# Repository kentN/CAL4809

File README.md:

# CAL4809
ATmega4809 TimeKeeping Module with MemoryLCD

----------

## Features ##

- ATmega4809 MCU (SRAM 6kB, FlashROM 48kB)
- Sharp Memory LCD (128x128pixcel or 96x96pixcel)
- 3 button
- Low Power Accelerometer ADXL362
- IrDA SIR Transceiver
- 32.768kHz External Crystal
- CR2032 Coin Cell battery (Diode OR option)
- External Connector(DF12-20p) 
- BUS UART(x2ch), SPI, I2C, GPIO/ADC(x8ch)

----------
## Applications ##

- DIY WristWatch
- Embedded Display&TimeKeeping module
- Motion Data Logger

----------

## Project Environment ##

- KiCad (5.0.1)
- Atmel Studio 7.0

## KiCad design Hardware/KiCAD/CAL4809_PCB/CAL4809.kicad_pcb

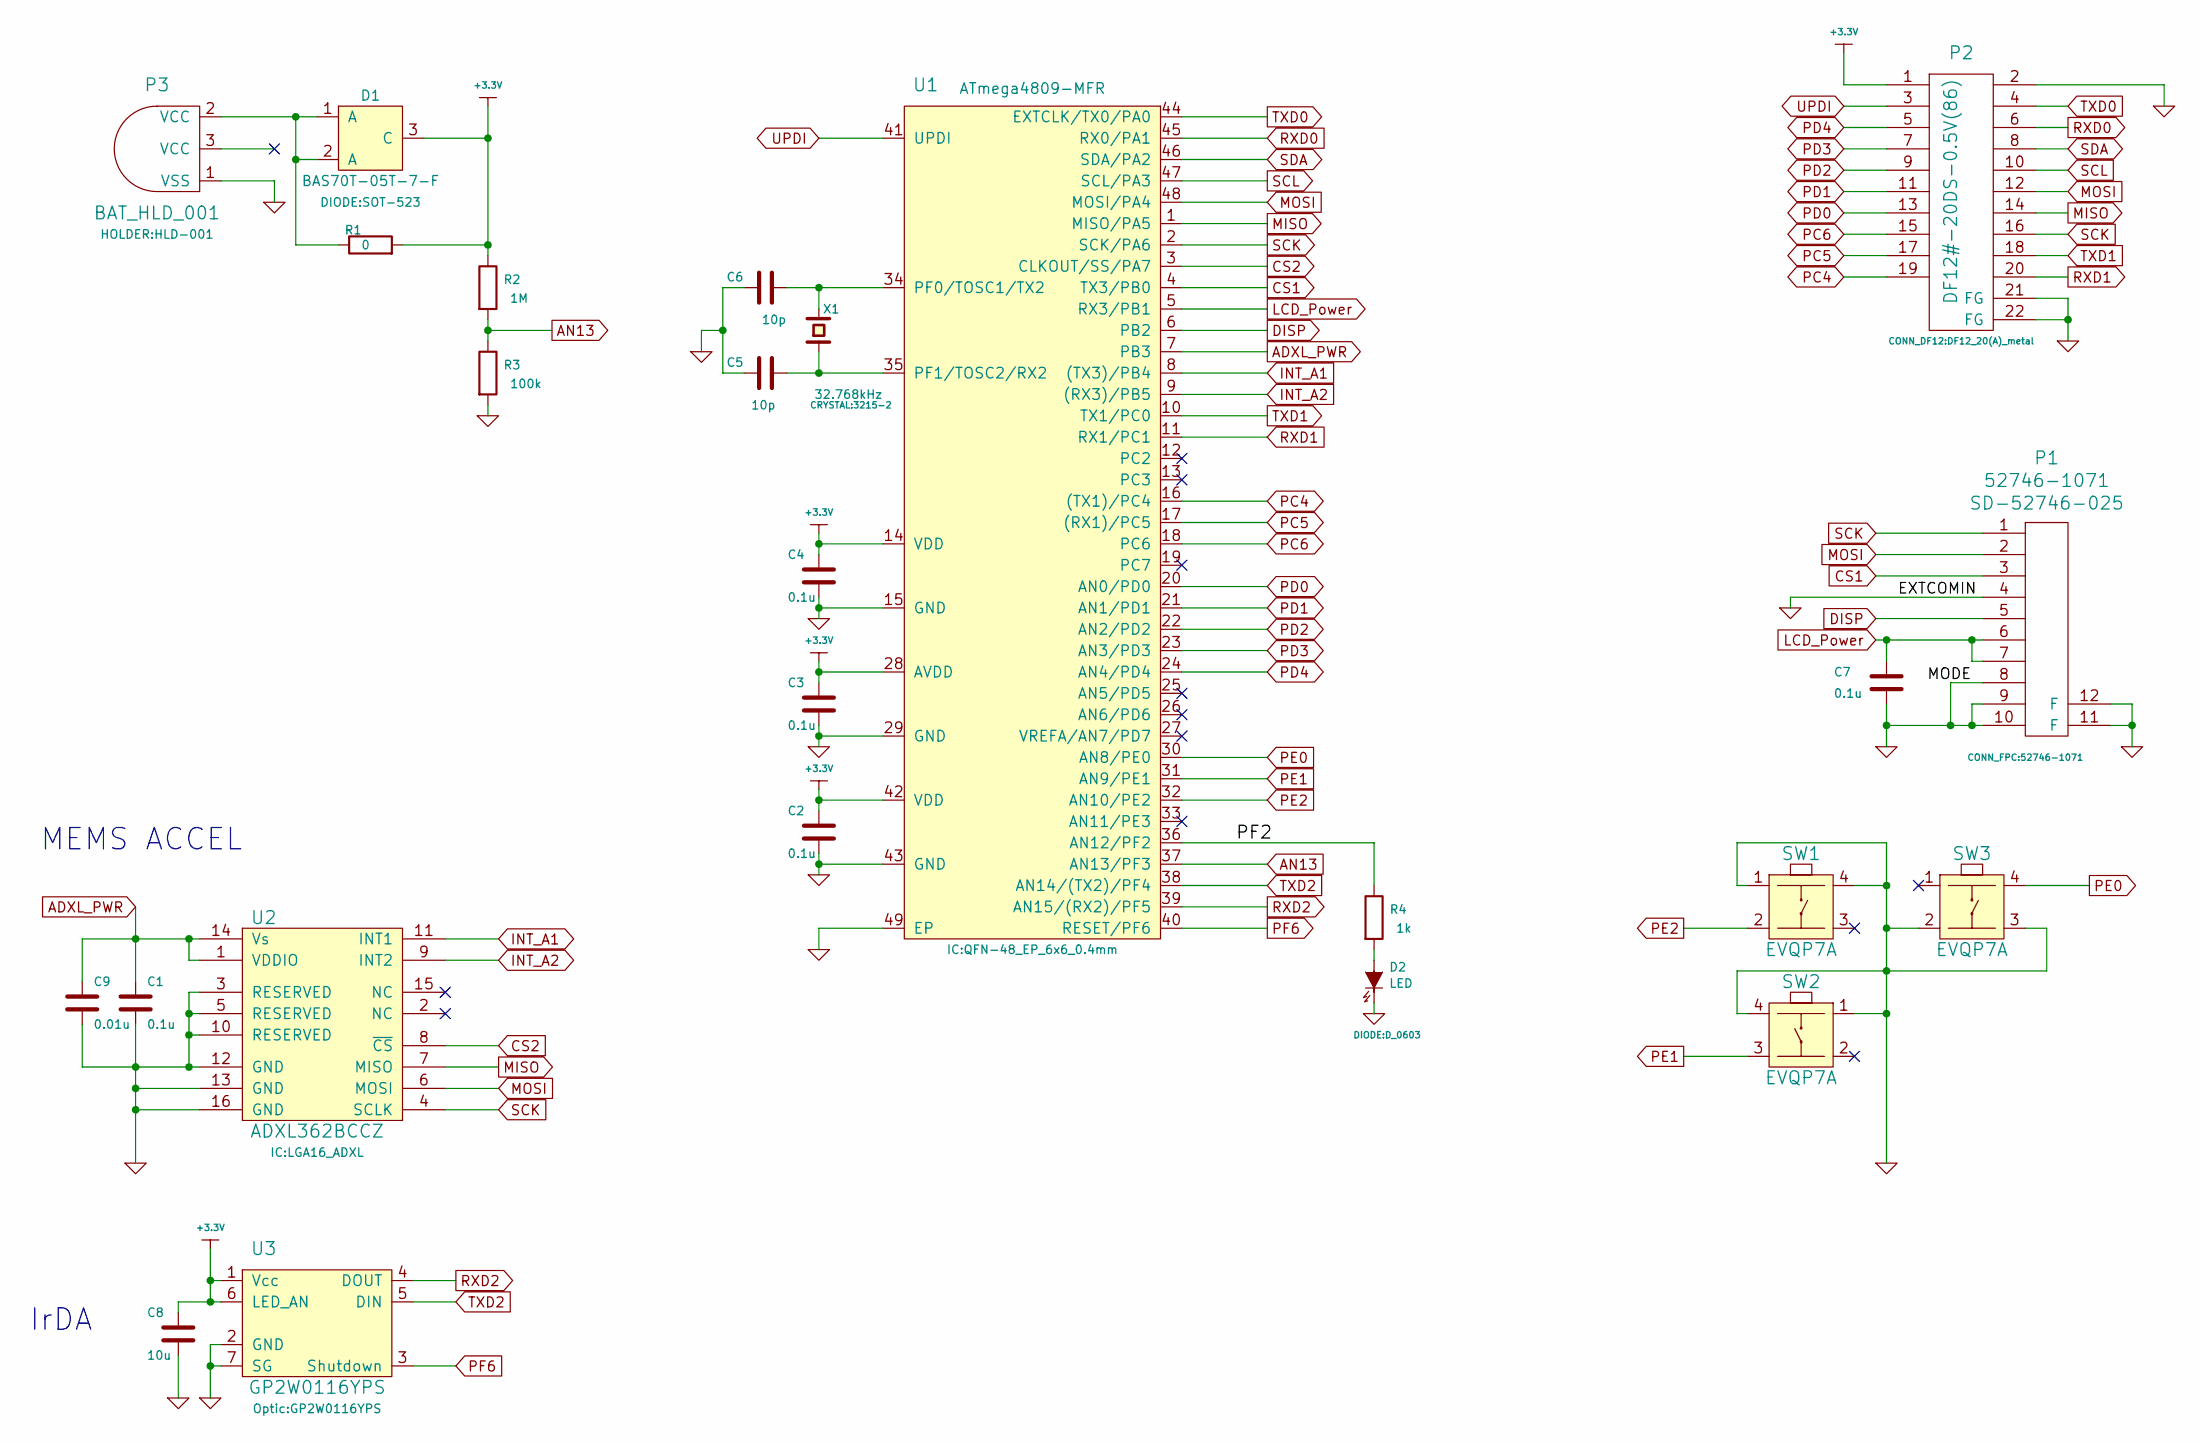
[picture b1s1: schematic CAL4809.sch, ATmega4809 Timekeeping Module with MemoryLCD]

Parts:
C1, C2, C3, C4, C7: 0.1u; 0402L
C5, C6: 10p; 0402L
C8: 10u; 0402L
C9: 0.01u; 0402L
D1: BAS70T-05T-7-F; SOT-523
D2: LED; D_0603
P1: 52746-1071
P2: DF12#-20DS-0.5V(86); DF12_20(A)_metal
P3: BAT_HLD_001; HLD-001
R1: 0; 0402L
R2: 1M; 0402L
R3: 100k; 0402L
R4: 1k; 0402L
SW1, SW2, SW3: EVQP7A
U1: ATmega4809-MFR; QFN-48_EP_6x6_0.4mm
U2: ADXL362BCCZ; LGA16_ADXL
U3: GP2W0116YPS
X1: 32.768kHz; 3215-2

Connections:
+3.3V: C2.1, C3.1, C4.1, C8.1, D1.3 (C), P2.1, R1.2, R2.1, U1.14 (VDD), U1.28 (AVDD), U1.42 (VDD), U3.1 (Vcc), U3.6 (LED_AN)
/PF2: R4.1, U1.36 (AN12/PF2)
ADXL_PWR: C1.1, C9.1, U1.7 (PB3), U2.1 (VDDIO), U2.14 (Vs)
AN13: R2.2, R3.1, U1.37 (AN13/PF3)
CS1: P1.3, U1.4 (TX3/PB0)
CS2: U1.3 (CLKOUT/SS/PA7), U2.8 (~CS)
DISP: P1.5, U1.6 (PB2)
GND: C1.2, C2.2, C3.2, C4.2, C5.2, C6.2, C7.2, C8.2, C9.2, D2.2 (K), P1.4, P1.8, P1.9, P1.10, P1.11 (F), P1.12 (F), P2.2, P2.21 (FG), P2.22 (FG), P3.1 (VSS), R3.2, SW1.1, SW1.4, SW2.1, SW2.4, SW3.2, SW3.3, U1.15 (GND), U1.29 (GND), U1.43 (GND), U1.49 (EP), U2.3 (RESERVED), U2.5 (RESERVED), U2.10 (RESERVED), U2.12 (GND), U2.13 (GND), U2.16 (GND), U3.2 (GND), U3.7 (SG)
INT_A1: U1.8 ((TX3)/PB4), U2.11 (INT1)
INT_A2: U1.9 ((RX3)/PB5), U2.9 (INT2)
LCD_Power: C7.1, P1.6, P1.7, U1.5 (RX3/PB1)
MISO: P2.14, U1.1 (MISO/PA5), U2.7 (MISO)
MOSI: P1.2, P2.12, U1.48 (MOSI/PA4), U2.6 (MOSI)
unnamed: C5.1, U1.35 (PF1/TOSC2/RX2), X1.1
unnamed: C6.1, U1.34 (PF0/TOSC1/TX2), X1.2
unnamed: D1.1 (A), D1.2 (A), P3.2 (VCC), R1.1
unnamed: D2.1 (A), R4.2
PC4: P2.19, U1.16 ((TX1)/PC4)
PC5: P2.17, U1.17 ((RX1)/PC5)
PC6: P2.15, U1.18 (PC6)
PD0: P2.13, U1.20 (AN0/PD0)
PD1: P2.11, U1.21 (AN1/PD1)
PD2: P2.9, U1.22 (AN2/PD2)
PD3: P2.7, U1.23 (AN3/PD3)
PD4: P2.5, U1.24 (AN4/PD4)
PE0: SW3.4, U1.30 (AN8/PE0)
PE1: SW2.3, U1.31 (AN9/PE1)
PE2: SW1.2, U1.32 (AN10/PE2)
PF6: U1.40 (RESET/PF6), U3.3 (Shutdown)
RXD0: P2.6, U1.45 (RX0/PA1)
RXD1: P2.20, U1.11 (RX1/PC1)
RXD2: U1.39 (AN15/(RX2)/PF5), U3.4 (DOUT)
SCK: P1.1, P2.16, U1.2 (SCK/PA6), U2.4 (SCLK)
SCL: P2.10, U1.47 (SCL/PA3)
SDA: P2.8, U1.46 (SDA/PA2)
TXD0: P2.4, U1.44 (EXTCLK/TX0/PA0)
TXD1: P2.18, U1.10 (TX1/PC0)
TXD2: U1.38 (AN14/(TX2)/PF4), U3.5 (DIN)
UPDI: P2.3, U1.41 (UPDI)

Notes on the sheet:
IrDA
MEMS ACCEL

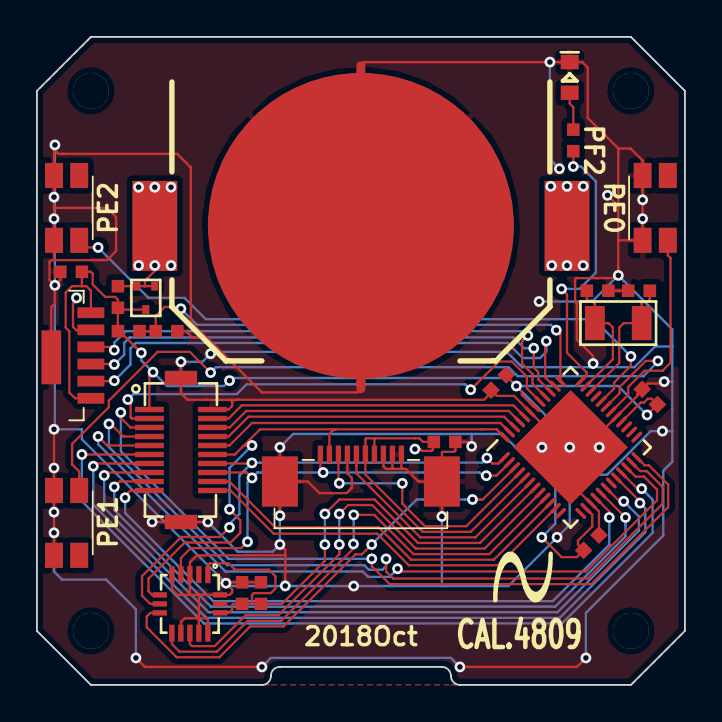
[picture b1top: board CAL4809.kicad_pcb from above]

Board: 2 copper layers, 36.0 x 36.0 mm, 29 parts (0 on the bottom side), 39 nets.

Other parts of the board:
Drill_M2, Drill_M2#2, Drill_M2#3, Drill_M2#4: VAL**; Drill_M2

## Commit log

2018-10-31 add CAL4809 kicad files
2018-11-07 Update Hardware/CAL4809_sch_revB.pdf
    add schematic pdf
2018-11-07 Update Hardware/CAL4809_pcb_revB.pdf
    add board layout
2019-01-31 add images
